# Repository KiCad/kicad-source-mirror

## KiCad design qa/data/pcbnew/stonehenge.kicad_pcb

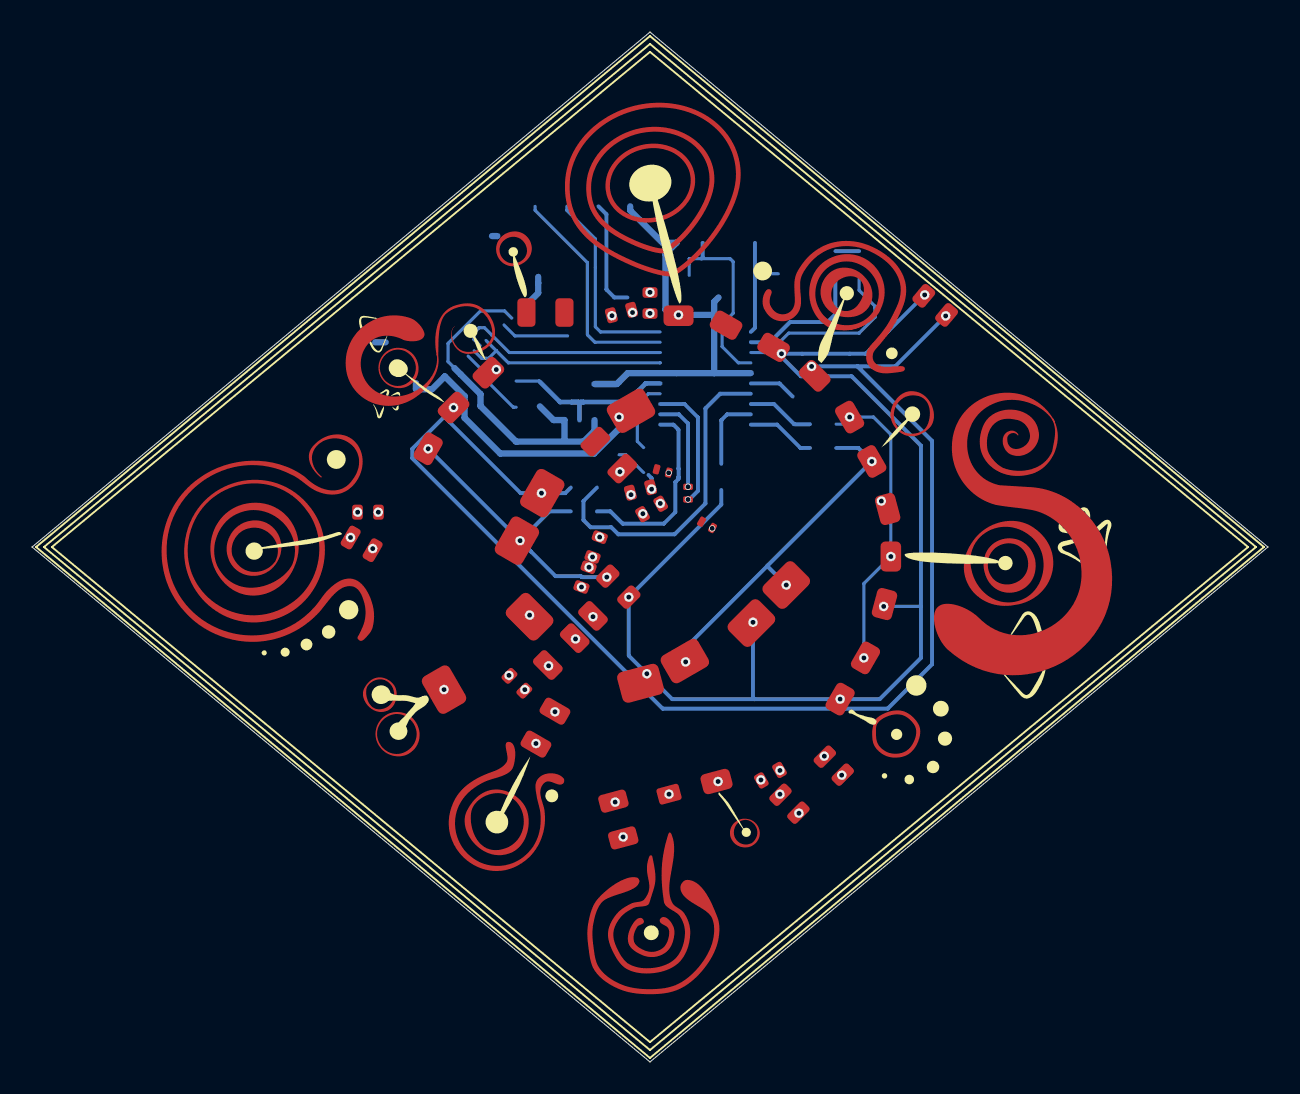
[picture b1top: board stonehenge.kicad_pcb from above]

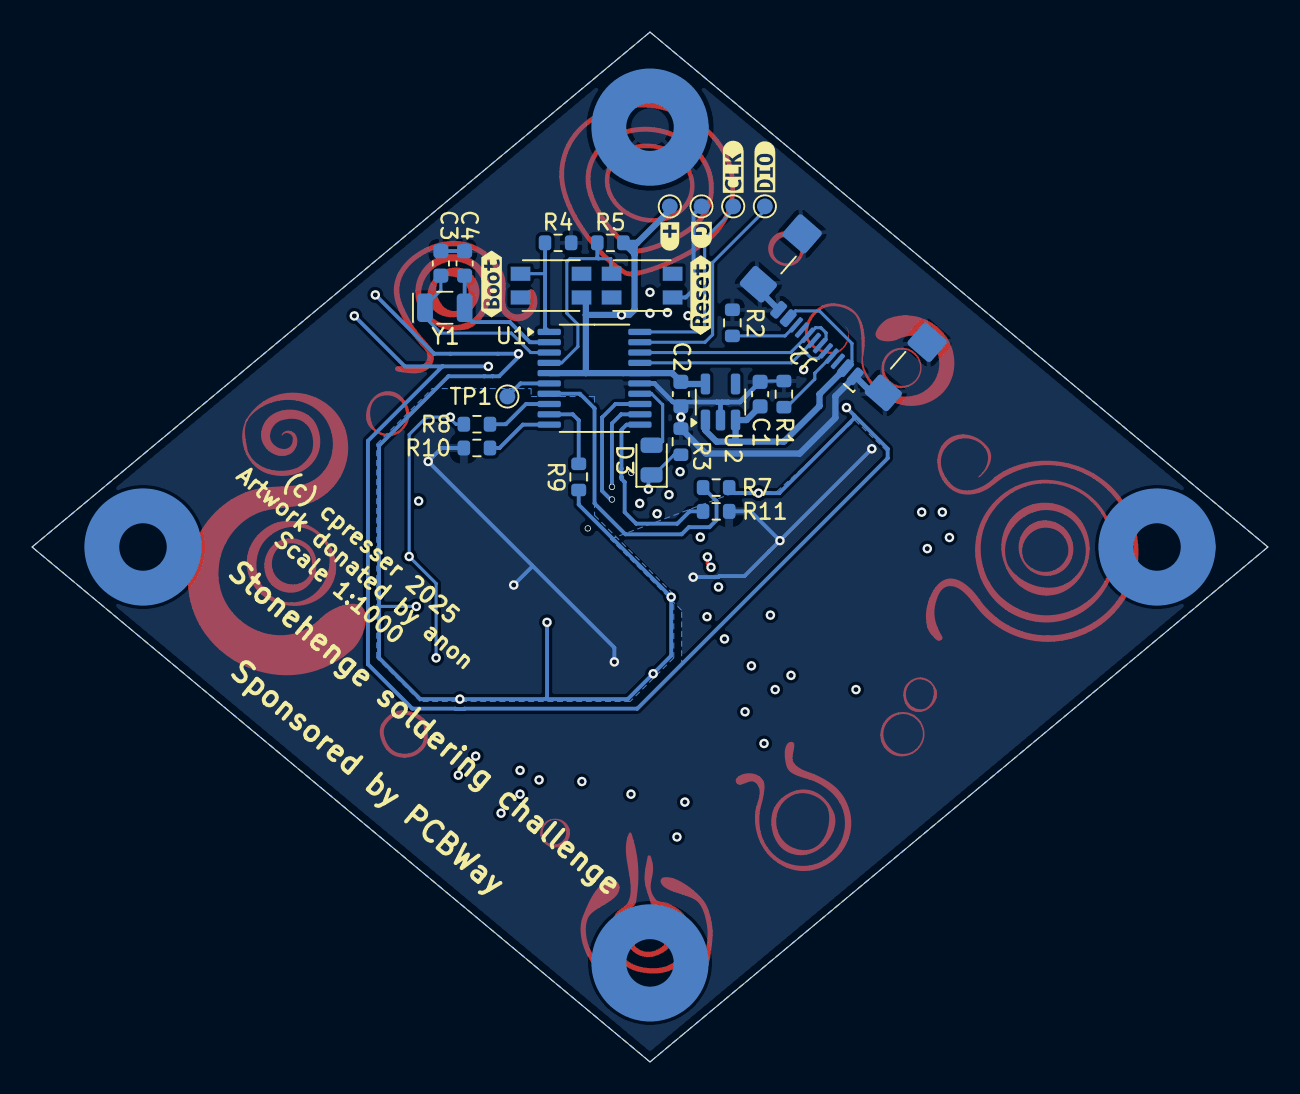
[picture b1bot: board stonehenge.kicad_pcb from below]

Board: 2 copper layers, 78.0 x 65.0 mm, 93 parts (36 on the bottom side), 29 nets.

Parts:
C1, C2: 1u; C_0603_1608Metric
C3, C4: 15p; C_0603_1608Metric
C8, C9b1, C19: C_0805; C_0805_Flat
C9a1, C15, C26, C59b1, C59c1, C120, C127, C156a1, C156b1: C_0603; C_0603_Flat
C12, C14, C25, C55b1, C59a1: C_1206; C_1206_Flat
C55a1: C_1206; C_1206_Angled
C160a1, C160b1, C160c1: C_0402; C_0402_Flat
D1: LED_0805; LED_0805_Altar
D2: LED_0805; LED_0805_Sun
D3: LED_0805; LED_0805_2012Metric
D101, D102, D105, D107, D122, D130: LED_1206; LED_1206_Reversed_Z1206
D152, D154, D158: LED_1206; LED_1206_Reversed_Z2010
H1, H2, H3, H4: MountingHole; Mounting_Wuerth_WA-SMSR-M3_H3.6mm_ReverseMount_9775036360_N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
J2: TYPE-C 16P QTWT; USB_C_Receptacle_SHOU-HAN_QTWT
L1, L2, L3, L4, L5, L6, L7, L10, L21, L22, L23, L27, L28, L29, L30: L_1206; L_1206_Upright
L11: L_0805; L_0805_Upright
L16, L51, L52, L53, L54, L56, L57, L58, L60: L_1806; L_2010_Upright
R1, R2, R4, R5: 5k1; R_0603_1608Metric
R3, R7, R8, R9, R10, R11: 47R; R_0603_1608Metric
SW1, SW2: YZA-011; SW_Push_1P1T_NO_YIZHI_YZA-011
TP1, TP3, TP4, TP5, TP7: TestPoint_Small; TestPoint_Pad_D1.0mm
U1: CH32V203F6P6; TSSOP-20_4.4x6.5mm_P0.65mm
U2: AP2112K-3.3; SOT-23-5
Y1: 12MHz; Crystal_SMD_MicroCrystal_CC7V-T1A-2Pin_3.2x1.5mm
kibuzzard-68CFE71F: G***; kibuzzard-68CFE71F
kibuzzard-68FE3E8F: G***; kibuzzard-68FE3E8F
kibuzzard-68FE3E82: G***; kibuzzard-68FE3E82
kibuzzard-68FE3EB2: G***; kibuzzard-68FE3EB2
kibuzzard-6882A3B6: G***; kibuzzard-6882A3B6
kibuzzard-6882A3CC: G***; kibuzzard-6882A3CC

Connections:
+3.3V: C2.1, L27.1, R5.2, SW2.1, TP7.1, U1.5 (VDDA), U1.16 (VDD), U2.5 (VOUT)
/D5: D2.1 (K), L22.1, L30.1, L58.1, R7.1
/D6: L1.1, L4.1, L6.1, R8.1
/D7: D1.1 (K), D2.2 (A), L5.1, L7.1, L29.1, L52.1, L54.1, R9.1
/D8: L2.1, L51.1, L53.1, R10.1
/D9: D1.2 (A), L21.1, L57.1, R11.1
/DM: J2.A7 (D-), J2.B7 (D-), U1.17 (USBDM)
/DP: J2.A6 (D+), J2.B6 (D+), U1.18 (USBDP)
/L: C59b1.2, D3.1 (K), R3.1
/PA6: C160b1.2, U1.12 (PA6)
/PA7: C160b1.1, U1.13 (PA7)
/SWCLK: TP3.1, U1.20 (SWCLK)
/SWDIO: TP4.1, U1.19 (SWDIO)
GND: C1.2, C2.2, C3.2, C4.2, H1.1, J2.A1 (GND), J2.A12 (GND), J2.B1 (GND), J2.B12 (GND), J2.S1 (SHIELD), L60.1, R1.2, R2.1, R3.2, R4.1, SW1.2, TP5.1, U1.15 (VSS), U2.2 (GND)
unnamed: C156a1.2, C156b1.2
unnamed: D3.2 (A), U1.14 (PB1)
unnamed: J2.A5 (CC1), R1.1
unnamed: J2.B5 (CC2), R2.2
unnamed: R4.2, SW2.2, U1.1 (BOOT0)
unnamed: C4.1, U1.2 (PD0), Y1.2
unnamed: C3.1, U1.3 (PD1), Y1.1
unnamed: TP1.1, U1.6 (PA0)
unnamed: R7.2, U1.7 (PA1)
unnamed: R8.2, U1.8 (PA2)
unnamed: R9.2, U1.9 (PA3)
unnamed: R10.2, U1.10 (PA4)
unnamed: R11.2, U1.11 (PA5)
unnamed: R5.1, SW1.1, U1.4 (~RST)
VBUS: C1.1, J2.A4 (VBUS), J2.A9 (VBUS), J2.B4 (VBUS), J2.B9 (VBUS), U2.1 (VIN), U2.3 (EN)
